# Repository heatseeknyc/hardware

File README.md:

## Heat Seek NYC Hardware

### Overview

connect XBee to the π via serial GPIO pins

listen for IO frames, which are of the form 0x7E....92

use a (manually maintained) mapping of 64-bit sensor addresses to apartments, to record apartment temperatures

### XBee-DigiMesh

Unlike XBee Zigbee, it supports synchronized sleeping, for low-power meshing.

The [chip](http://www.digikey.com/product-detail/en/XB24-DMPIT-250/602-1338-ND/3482610) — this is the same hardware as [XBee Series 1](http://www.digikey.com/product-detail/en/XB24-API-001/602-1273-ND/3482588) but with DigiMesh firmware pre-installed.

The [docs](http://ftp1.digi.com/support/documentation/90000991_L.pdf).

Adding a new node is slightly trickier, but if the π node is in "Synchronous Sleep Support Mode" SM=7, then you can just bring a new node near the π at any time and it will sync up with the rest of the sleeping (SM=8) nodes.

### Alternatives

#### XBee-Zigbee

Can't both sleep and mesh, but has a better ADC, perhaps among other things.

Make sure to connect VREF to VCC. This is basically undocumented, but without it the chip basically crashes after a minute of reading from the ADC. _TODO_ email Digi about this.

The [chip](http://www.digikey.com/product-detail/en/XB24-Z7PIT-004/602-1275-ND/3482624), aka XBee Series 2.

The [docs](http://ftp1.digi.com/support/documentation/90000976_S.pdf)

### GERBER Files
If you need to generate a GERBER file, follow the instructions in [this tutorial](https://learn.sparkfun.com/tutorials/using-eagle-board-layout/generating-gerbers). You just clone [their repo](https://github.com/sparkfun/SparkFun_Eagle_Settings) and use `sfe-gerb274x.cam`.

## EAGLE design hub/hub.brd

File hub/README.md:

# Hub node

## Serial connection

- GPIO pin 1 (3v3) to XBee pin 1 (VCC)
- GPIO pin 6 (GND) to XBee pin 10 (GND)
- GPIO pin 8 (TXD) to XBee pin 3 (DIN)
- GPIO pin 10 (RXD) to XBee pin 2 (DOUT)

## Data usage

Assuming each reading is ~100 bytes (the reading itself may be as little as 20-30 bytes, plus the HTTP headers), and each cell takes 24 readings per day, that's 24 x 100 = 2,400 bytes per day per cell, or 2.4 kilobytes (roughly, 1kb = 1024b).

Assuming a base is connected to 10 cells, then the base will be transmitting 10 x 2.4 = 24 kilobytes per day.
Assuming 31 days per month (worst case), and 365 days per year, data usage will be:

|numCells|Data/Day|Data/Month|Data/120d|Data/Year|
|--------|--------|----------|---------|---------|
|1       |2.4 kb  |0.0744 mb |0.288 mb |0.876 mb |
|10      |24 kb   |0.744 mb  |2.88 mb  |8.76 mb  |
|15      |36 kb   |1.17 mb   |4.32 mb  |13.14 mb |
|20      |48 kb   |1.48 mb   |5.76 mb  |17.52 mb |
|30      |72 kb   |2.23 mb   |8.64 mb  |26.28 mb |
|50      |120 kb  |3.72 mb   |14.4 mb  |43.8 mb  |
|100     |240 kb  |7.44 mb   |28.8 mb  |87.6 mb  |

Pre-paid Vodafone SIM cards:
- [1MB/month for a year](http://www.embeddedworks.net/wsim2730.html) for $31.27, or $2.61/MB
- [5MB/month for 6 months](http://www.embeddedworks.net/wsim2737.html) for $46.11, or $1.54/MB
- [10MB/month for a year](http://www.embeddedworks.net/wsim2786.html) for $137.41, or $1.15/MB

## 3G modems

There's a [generic stick](http://www.amazon.com/Generic-Wireless-7-2Mbps-Dongle-Function/dp/B00MHAKIJY/ref=sr_1_10?ie=UTF8&qid=1410451158&sr=8-10&keywords=usb+modem+wireless) for ~$13 and a [branded alternative](http://www.amazon.com/Huawei-E173-Unlocked-HSDPA-7-2Mbps/dp/B0055310KQ) for ~$26. Given that we currently budget $6 for a USB WiFi dongle, each of these represents some increase to the cost of the base, $7 and $20, respectively.

[Verified 3G USB dongles](http://elinux.org/RPi_VerifiedPeripherals#USB_3G_Dongles)

## Alternatives

connect the HSDPA (3G) dongle to an [Arduino USB Host Shield](https://www.sparkfun.com/products/9947), to see how easy direct USB 3G modem AT commands are... possibly not easy.

connect a [FONA GSM (2G) board](https://www.adafruit.com/fona) to an Arduino or whatever. this isn't cheaper than a Raspberry Pi, but could lead to a cheaper PCB.

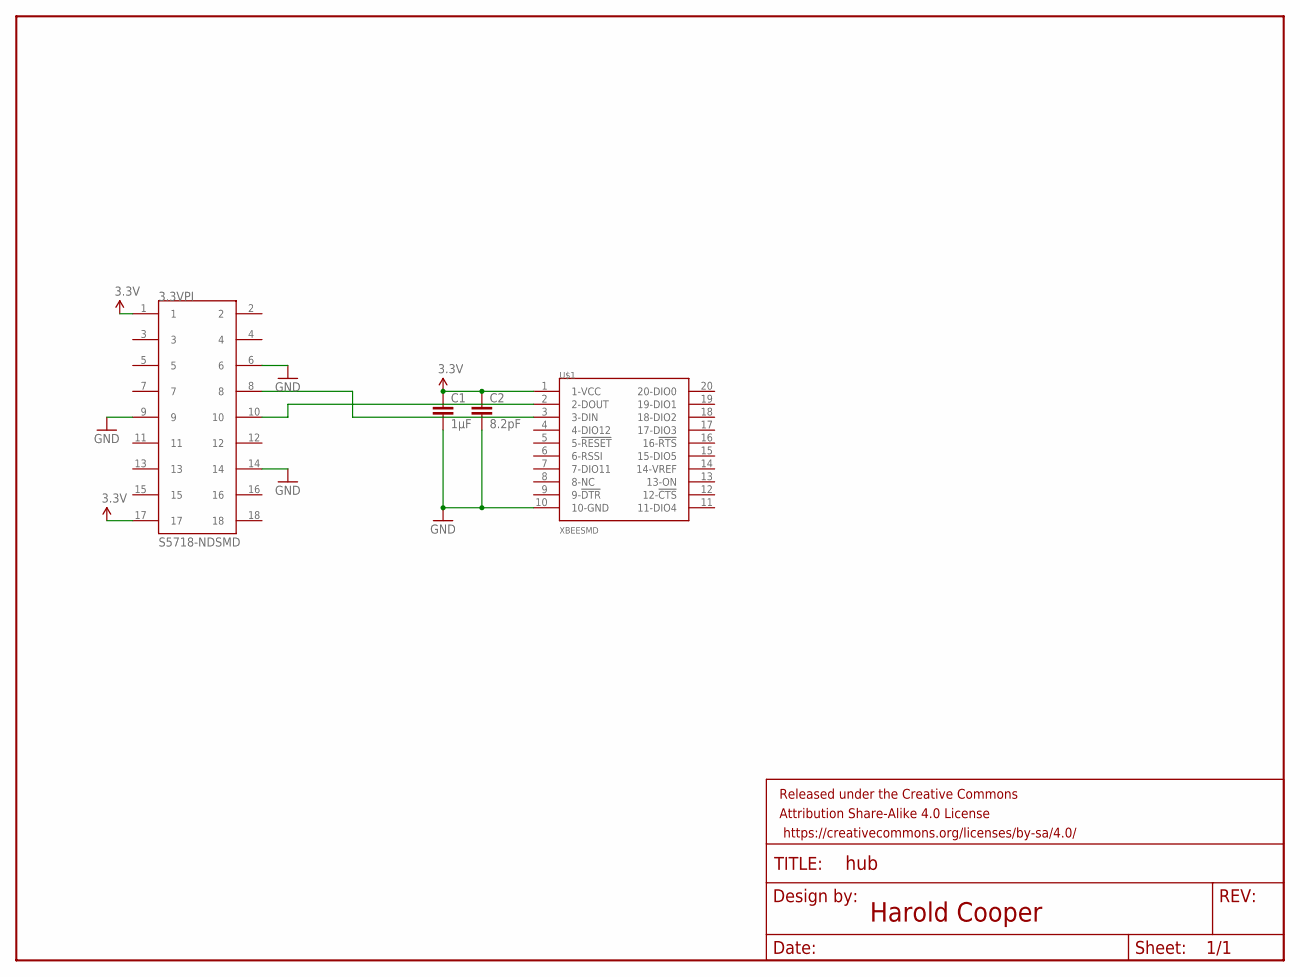
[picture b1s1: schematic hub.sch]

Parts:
3.3VPI: S5718-NDSMD; CONN_HEADER_SMD_18
C1: 1µF; 0805
C2: 8.2pF; 0805
FRAME1: FRAME-LETTER; CREATIVE_COMMONS
U$1: XBEESMD; CONN_HEADER_SMD_10X2

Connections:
3.3V: 3.3VPI.1, 3.3VPI.17, C1.1, C2.1, U$1.1 (1-VCC)
GND: 3.3VPI.6, 3.3VPI.9, 3.3VPI.14, C1.2, C2.2, U$1.10 (10-GND)
unnamed: 3.3VPI.10, U$1.2 (2-DOUT)
unnamed: 3.3VPI.8, U$1.3 (3-DIN)

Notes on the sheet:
Harold Cooper

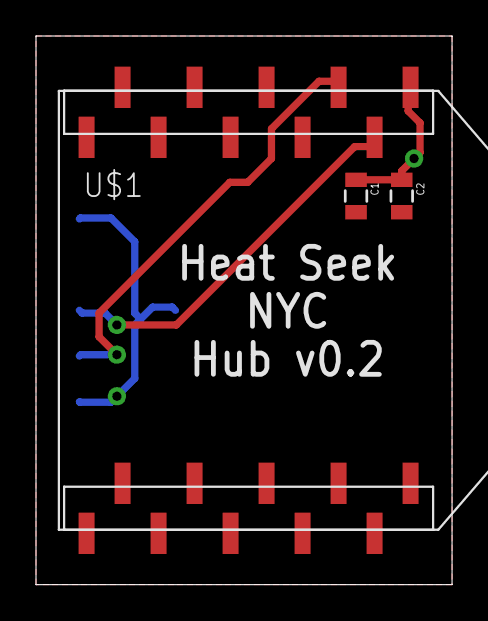
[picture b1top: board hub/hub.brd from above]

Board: 2 copper layers, 23.1 x 30.5 mm, 5 parts (0 on the bottom side), 4 nets.

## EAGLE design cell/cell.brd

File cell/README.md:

# Cell node

## Electrical

### Components

See the [spreadsheet](https://docs.google.com/spreadsheets/d/1aLX0yPriqRYv9exc7hV8ZaoWDZZKsPV997NUnLpyvPM/edit?usp=sharing).

#### Searching for capacitors
for now we're using Kemet X7R 50V ±10% ceramic 0805s and through-hole radial capacitors

so to search go [here](http://www.digikey.com/product-search/en?v=399&pv14=32&pv16=2&pv16=6&FV=fff40002%2Cfff8000b&stock=1&pbfree=1&rohs=1) and then filter by capacitance

#### Temperature Sensor Chips
- our current chip: [surface mount analog temperature sensor](http://www.digikey.com/product-detail/en/MCP9700AT-E%2FTT/MCP9700AT-E%2FTTCT-ND/3622388) ±2°C from 0°C to 70°C, $0.24
- [surface mount RTD](http://www.digikey.com/product-detail/en/PTS080501B500RP100/PTS0805500CT-ND/1666191) ±0.5°C from -40°C to 40°C, $1.91
- [surface mount analog temperature sensor](http://www.digikey.com/product-detail/en/DS600U%2B/DS600U%2B-ND/1197625), ±0.5°C from -20°C to 100°C, $2.58
- [ball grid array analog temperature sensor](http://www.digikey.com/product-detail/en/LMT70YFQT/296-42088-1-ND/5252841) ±0.2°C from -20°C to 90°C, $1.73

### Power consumption

The input range of the MCP1700 is about 3.5V to absolute maximum 6.5V,
so we use 4xAAA batteries, which gives us an initial voltage of about 6.4V, and a voltage of about 4V after 1000mAh.

- MCP1700 quiescent current < 4µA
- XBee cyclic sleep current < 50µA
- Xbee transmit current < 45mA / 250mA PRO
- XBee idle/receive current < 50mA / 55mA PRO
- XBee ADC current **??**
- MCP9700 operating current < 12µA

**TODO** measure these!
- total sleeping current < 54µA
- total waking current < 50mA / 250mA PRO

#### Setup mode

If we transmit constantly, we use 50mA / 250mA PRO, so every hour of setup we use 1.3% / 6.3% PRO of the batteries.

#### Live mode

So if we transmit for 5 seconds every hour, we use 124µAh / 402µAh PRO per hour, so 4x1000mAh battery would last 3.6 / 1.1 PRO years.

And if we transmit for 10 seconds every hour, we use 193µAh / 749µAh PRO per hour, so 4x1000mAh battery would last 2.3 / 0.6 PRO years.

## Mechanical

### flat battery holder mounting

assuming symmetry, mounting hole centers are offset from left and right edges by (1.98" - 0.5") / 2 = 0.74"

terminals are offset from bottom by 0.102"

### XBee dimensions, including *full height* of [socket](http://www.sullinscorp.com/drawings/75_1BFC_10483.pdf)

XBee is smaller than XBee-PRO, `32.94mm - 5.33mm = 27.61mm`

    24.38mm W x 27.61mm D x 9.79mm (2.79mm + 7.0mm) H

### battery holder dimensions

[3d model](flat-case-squat-case-and-us-quarter.stl) of flat and squat cases and a quarter

#### [flat](http://www.digikey.com/product-detail/en/2481/2481K-ND/303826)

    50.79mm W x 54.51mm D x 23.29mm (13.5mm + 9.79mm) H
    2.00" W x 2.15" D x 0.92" H

#### [squat](http://www.digikey.com/product-detail/en/BH24AAAW/BH24AAAW-ND/38633)

    26mm W x 53mm D x 35mm (25mm + 10mm) H

### cases

#### [TS-3315P](http://www.polycase.com/ts-3315p)

    3.00" x 3.00" x 1.50", weight=2.1oz, volume=13.5""", price=$2.05

#### [LP-41P](http://www.polycase.com/lp-41p)

    3.29" x 3.29" x 1.25", weight=3.2oz, volume=13.53""", price=$2.66

#### [CU-791](http://www.budind.com/view/Plastic+Boxes/Utilibox+Style+E)

    3.08" x 3.08" x 1.50", weight=1.5oz, volume=14.23""", price=$2.86

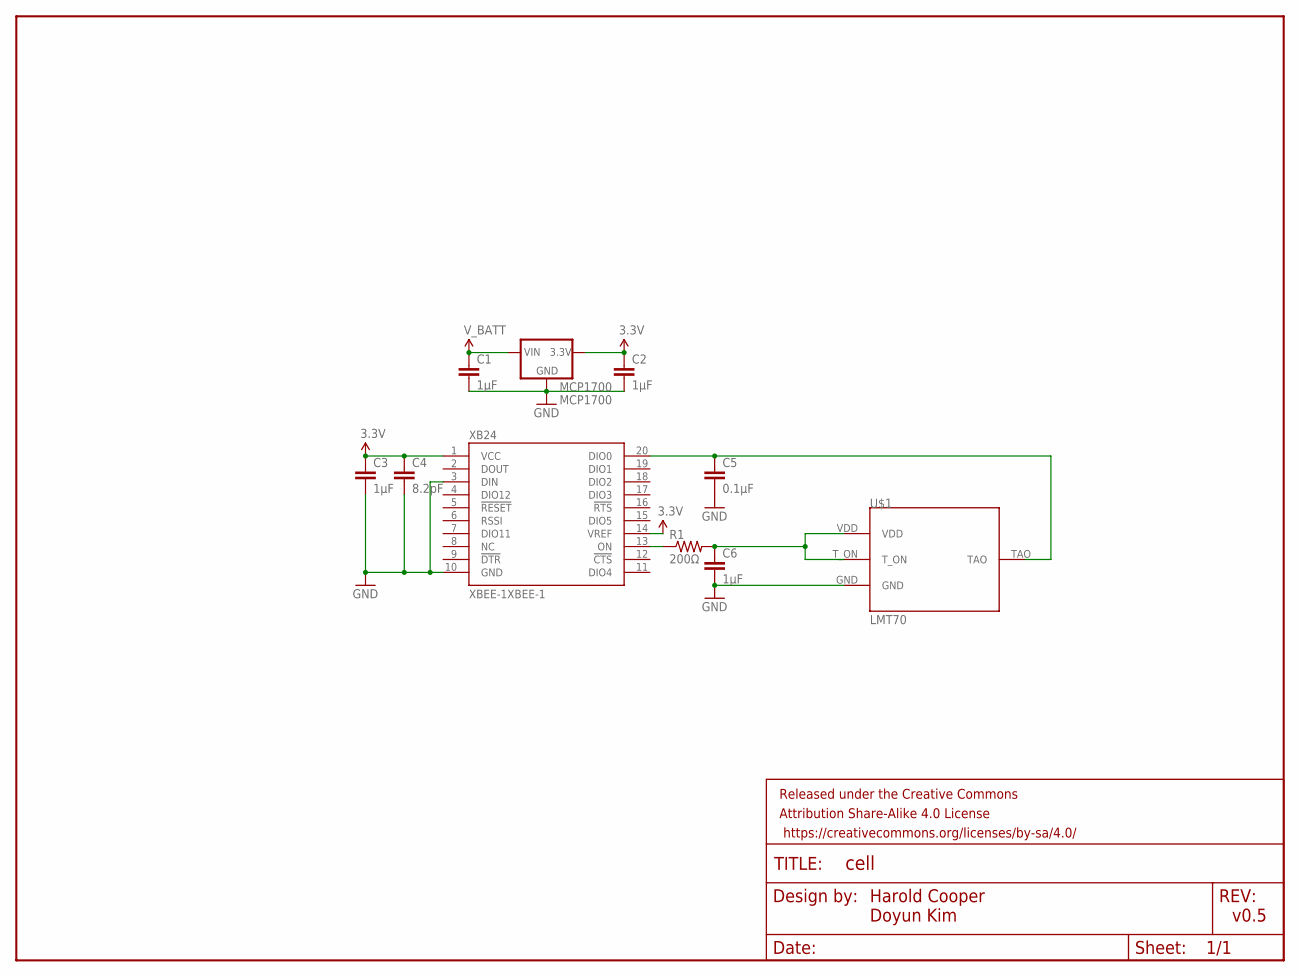
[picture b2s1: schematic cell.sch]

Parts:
C1, C2, C3, C6: 1µF; 0805
C4: 8.2pF; 0805
C5: 0.1µF; 0805
FRAME1: FRAME-LETTER; CREATIVE_COMMONS
MCP1700: MCP1700; SOT-89-3
R1: 200Ω; 0805
U$1: LMT70; YFP0004
XB24: XBEE-1XBEE-1; XBEE-1

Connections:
3.3V: C2.1, C3.1, C4.1, MCP1700.3 (3.3V), XB24.1 (VCC), XB24.14 (VREF)
GND: C1.2, C2.2, C3.2, C4.2, C5.2, C6.2, MCP1700.1 (GND), U$1.GND, XB24.3 (DIN), XB24.10 (GND)
unnamed: C6.1, R1.2, U$1.T_ON, U$1.VDD
unnamed: R1.1, XB24.13 (ON)
unnamed: C5.1, U$1.TAO, XB24.20 (DIO0)
V_BATT: C1.1, MCP1700.2 (IN)

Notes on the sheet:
Harold Cooper Doyun Kim
v0.5

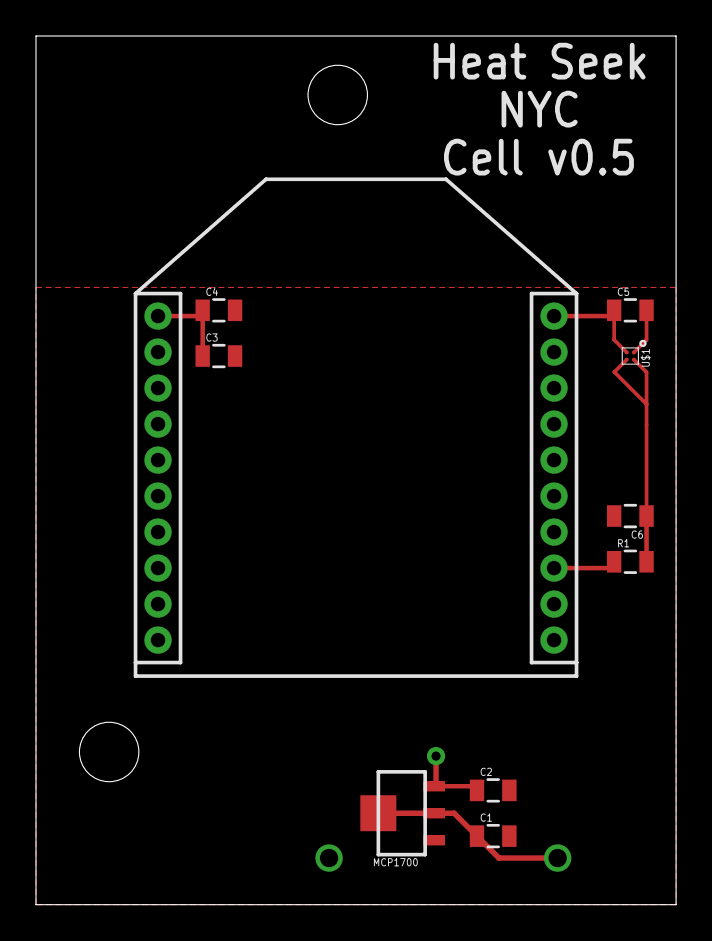
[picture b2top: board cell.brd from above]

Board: 2 copper layers, 35.6 x 48.3 mm, 11 parts (0 on the bottom side), 6 nets.

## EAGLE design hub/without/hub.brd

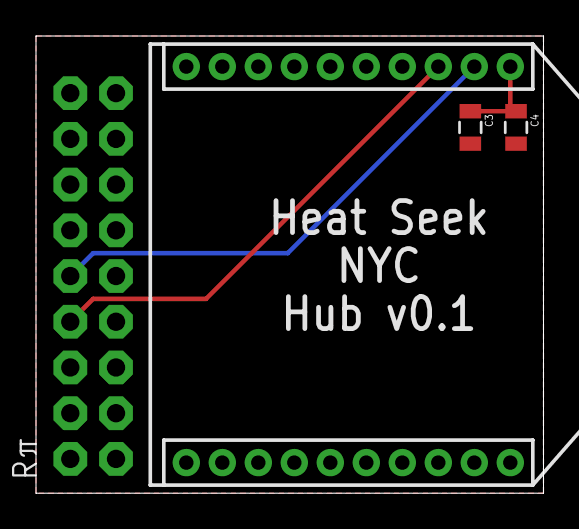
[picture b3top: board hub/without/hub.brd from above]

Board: 2 copper layers, 28.2 x 25.4 mm, 5 parts (0 on the bottom side), 4 nets.

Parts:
C3: 1µF; 0805
C4: 8.2pF; 0805
FRAME1: FRAME-LETTER; CREATIVE_COMMONS
Rπ: M9X2; 2X9_NOSILK
XB24: XBEE-1XBEE-1; XBEE-1

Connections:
3.3V: C3.1, C4.1, Rπ.1, Rπ.17, XB24.1
GND: C3.2, C4.2, Rπ.6, Rπ.9, Rπ.14, XB24.10
unnamed: Rπ.10, XB24.2
unnamed: Rπ.8, XB24.3

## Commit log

2014-06-17 markdown
2014-06-17 note about weird ADC
2014-06-17 DIO0 defaults to "commissioning button" so we'll leave it alone and use the disabled AD1
2014-07-12 script for parsing xbee sensor readings from serial
2014-07-16 moved rasberry pi files to the hardware repo
2014-07-17 ignore emacs backups
2014-07-17 remove ftdi_sio
2014-07-17 readme
2014-07-17 better name
2014-07-17 pylibftdi support
2014-07-17 FTDI notes
2014-07-18 doing our own buffering makes pylibftdi work great! removed 'serial' library support. outputting tsv, with an additional signature column.
2014-07-18 files without final newlines are annoying, so start using puts to write sofar.txt
2014-07-18 since we are reading from a file that is actively being written, we'll avoid the last line in case it's incomplete
2014-07-18 delimit with tabs for readability
2014-07-18 round times and temperatures, don't truncate
2014-07-18 remove binding
2014-07-18 manually set uri.hostname and uri.port
2014-07-18 moved data into data/ directory, which is gitignored. renamed 'sofar.txt' to 'progress'
2014-07-18 loop transmit script forever
2014-07-18 rename read_xbee to receive, consistent with transmit
2014-07-18 gitignore nohup.out
2014-07-18 demo notes
2014-07-18 eventually we'll want these init scripts
2014-07-19 demo instructions using a screen, for easier debugging
2014-08-01 DigiMesh notes
2014-08-02 link to ZB24-PIT chip and docs
2014-08-08 digimesh battery life caclulations
2014-08-29 encryption note
2014-09-04 various changes from demo day
2014-09-04 simpler screen instructions
2014-09-04 screenrc can't do pipes
2014-09-04 print extra info after unsuccessful heatseek POSTs
2014-09-09 skip errors, and log stderr
2014-09-10 new plan for π serial
2014-09-12 added cellular analysis to readme
2014-09-12 formatting
2014-09-12 added table to readme
2014-09-12 formatted table
2014-09-12 updated table values
2014-09-12 added pro to cellular analysis
2014-09-12 updated cellular analysis
2014-09-12 3g usb π link
2014-09-13 link to the procurement spreadsheet
2014-09-13 vodafone sim cards
2014-09-13 robustness improvements
2014-09-14 raspi-config can disable serial
2014-09-14 go back to using serial, no more USB!
2014-09-14 serial pin connections
2014-09-14 pinout image
2014-09-14 use local image in readme
2014-09-15 preliminary 3G modem notes...
2014-09-16 now using XBee Series 1 ADCs
2014-09-16 ruby 1.9.3 compatible
2014-09-17 log adc details
2014-09-17 higher timeouts for 3g, more thorough screen
2014-09-17 data/ (re-)init script
2014-09-30 updated power consumption assuming 3xAAA
2014-10-01 initial cell schematic
2014-10-01 rename
2014-10-01 4xAAA
2014-10-02 ignore .DS_Store
2014-10-02 eagle files
2014-10-02 move cell/ to eagle/
2014-10-02 whoops we need to leave schematic.pdf there since we just linked to it on kickstarter :hear_no_evil:
2014-10-07 bottom offset is documented, doesn't need to be derived
2014-10-08 capacitors
2014-10-08 whoops search was axial not radial
2014-10-08 remove ±10% constraint, since smaller capacitors aren't listed that way
2014-10-08 remove X7R constraint, since smaller capacitors aren't listed that way
2014-10-10 add pcb text
2014-10-10 cell v0.1, as ordered from OSH Park on 2014-10-07
2014-10-10 pcb folder
2014-10-10 dimensions for both flat and "squat" battery holders
2014-10-10 links
2014-10-10 STL model of cases
2014-10-10 sketchup model
2014-10-10 ignore sketchup *~.skp files, and anything else like that
2014-10-10 link to 3d model
2014-10-13 using MCP9700A instead of TMP36
2014-10-13 cell, hub, and π folders
2014-10-18 README!!!
2014-11-03 π notes
2014-11-03 link to deployments spreadsheet
2014-11-03 smart quotes can go to hell
2014-11-03 who needs screen, tmux rules ;?j
2014-11-04 protect resolv.conf from dhclient and everyone else
2014-11-10 cell v0.2, with on-board temperature sensor and better layout
2014-11-11 cell v0.3, with power plane eliminating the major traces
2014-11-11 board images
2014-11-11 BOM and CPL spreadsheets
2014-11-11 ignore weird eagle intermediates
2014-11-11 increase width and isolation of pours, as per https://www.sparkfun.com/tutorials/115
2014-11-11 increase supply traces from 10mil to 12mil
2014-11-11 don't show names, turns out assembly shouldn't need them
2014-11-12 v0.3, with both OSH Park and FreeDFM previews
2014-11-13 5x2 cell array that Advanced Circuits is printing
2014-11-13 hub pcb v0.1
2014-11-13 gitignore gerbers
2014-11-14 same AT order as XCTU
2014-11-16 closest you can get to Bailey's without getting your nose wet
2014-11-16 use the largest header we can fit, for stability and to look cool?
2014-11-16 it's like the image of a stacked man
2014-11-16 higher-res osh park previews
2014-11-16 stacked/
2014-11-16 hub v0.1 osh park previews
2014-11-16 within/ for board that tries to fit inside case
2014-11-16 without/ for board outside of case, for Pimoroni A+ case
2014-11-16 tighter fit, turns out XBee fits perfectly on 1" wide board
2014-11-18 outside-of-case hub board previews
2014-11-19 more accurate cell dimensions
2014-11-19 final dimensions in inches as well
2014-11-19 possible cell cases
2014-11-27 rename chips
2015-01-05 DIN/!CONFIG pull-up resistor must not be disabled!
    see the WARNING here - http://www.digi.com/support/kbase/kbaseresultdetl?id=3522
    :sob:
2015-01-05 ground DIN/!CONFIG so that we can safely disable its pullup resistor
2015-01-05 reference new PR settings for new v0.4 cell board
2015-01-14 π keyboard layout defaults to UK
2015-01-15 correct a log message
2015-01-22 π is hard to type on linux :sob:
2015-01-23 store readings to sqlite
2015-01-23 rename receive.py to xbee_listener.py to make clear that it is long-running
2015-01-23 on second thought, 'receiver.py' is nice and simple
2015-01-23 use supervisor for wvdial, autossh, receiver, and (soon) transmitter
2015-01-24 move database to common.py, as a place to put any code used by both receiver and transmitter programs
2015-01-27 'conf' folder with supervisor and wvdial configs; 'hub' module for python code
2015-01-27 use new conf directory in README
2015-01-27 useful @forever decorator, and no need for custom read() method now that we've stopped using libftdi
2015-01-27 distinguish 'readings', which contain 'temperatures'. transmit raspberry pi serial number as hub id. store python dependencies in requirements.txt
2015-01-28 simpler pip installation
2015-01-28 beginnings of transmitter script
2015-01-28 update database upon successful transmission
2015-01-29 new script posts ssh port every time it changes
2015-01-29 store db schema in schema.sql
2015-01-29 just use normal ssh, with a null packet every minute
2015-01-29 TODO send hub's xbee id and send cellular network stats
2015-01-29 vnstat
2015-02-04 use network id of 311 (the number NYC residents call to report heating violations!); less likely to have conflicts with the default network id
2015-02-04 we never use NI
2015-02-04 note about potential for conflict between multiple hubs
2015-02-04 attempt to fix database locking bugs: Database must be used in a `with` statement, and closes its connection
2015-02-07 moved pi to heatseeknyc/pi
2015-02-08 moved firmware settings to heatseeknyc/pi
2015-02-22 updated power estimates, including XBee PRO
2015-02-24 pull-up resistors don't pull from ground, duh :sob:
2015-02-24 whoops math
2015-02-24 missing "PRO"
2015-11-16 list current and alternative temperature sensors
2015-11-27 replace MCP9700A with LMT70
2015-11-27 continues using sparkfun's eagle settings - https://github.com/sparkfun/SparkFun_Eagle_Settings/blob/master/scr/eagle.scr
2015-11-27 center LMT70 with other chips
2015-11-27 fix LMT70 naming
2015-11-29 OSH Park preview for cell v0.5
2015-11-30 FreeDFM preview for cell v0.5
2015-12-01 use symmetric traces on BGA chip, to avoid unequal soldering and tension
2015-12-02 use smallest traces allowed by TI's AN-1112 doc (205µm) and smallest soldermask swell allowed by Advanced Circuits (5mil) to maximize the amount of mask separating the pads. this gives a 332µm solder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
2015-12-22 get rid of 'within' hub board design, since we don't use it
2015-12-22 convert gimp file to png
2016-01-05 Add GERBER instructions to README, closes #3
2016-01-06 smd-ver
2016-01-27 drc error fixed and gerber files are created
2016-01-28 fix DRC angle errors by removing tiny traces
2016-01-28 don't track generated content
2016-02-06 Add updated BOM file for SMT components

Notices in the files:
parts and their libraries:
SparkFun-Aesthetics: Licensing: Creative Commons ShareAlike 4.0 International - https://creativecommons.org/licenses/by-sa/4.0
SparkFun-Aesthetics: Released under the Creative Commons Attribution Share-Alike 4.0 License
SparkFun-Aesthetics: https://creativecommons.org/licenses/by-sa/4.0
